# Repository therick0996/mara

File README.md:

# Patrick

**USE AT YOUR OWN RISK!!!** I am not responsible for any dumb things you do. Like fry your computer, break anything, etc.

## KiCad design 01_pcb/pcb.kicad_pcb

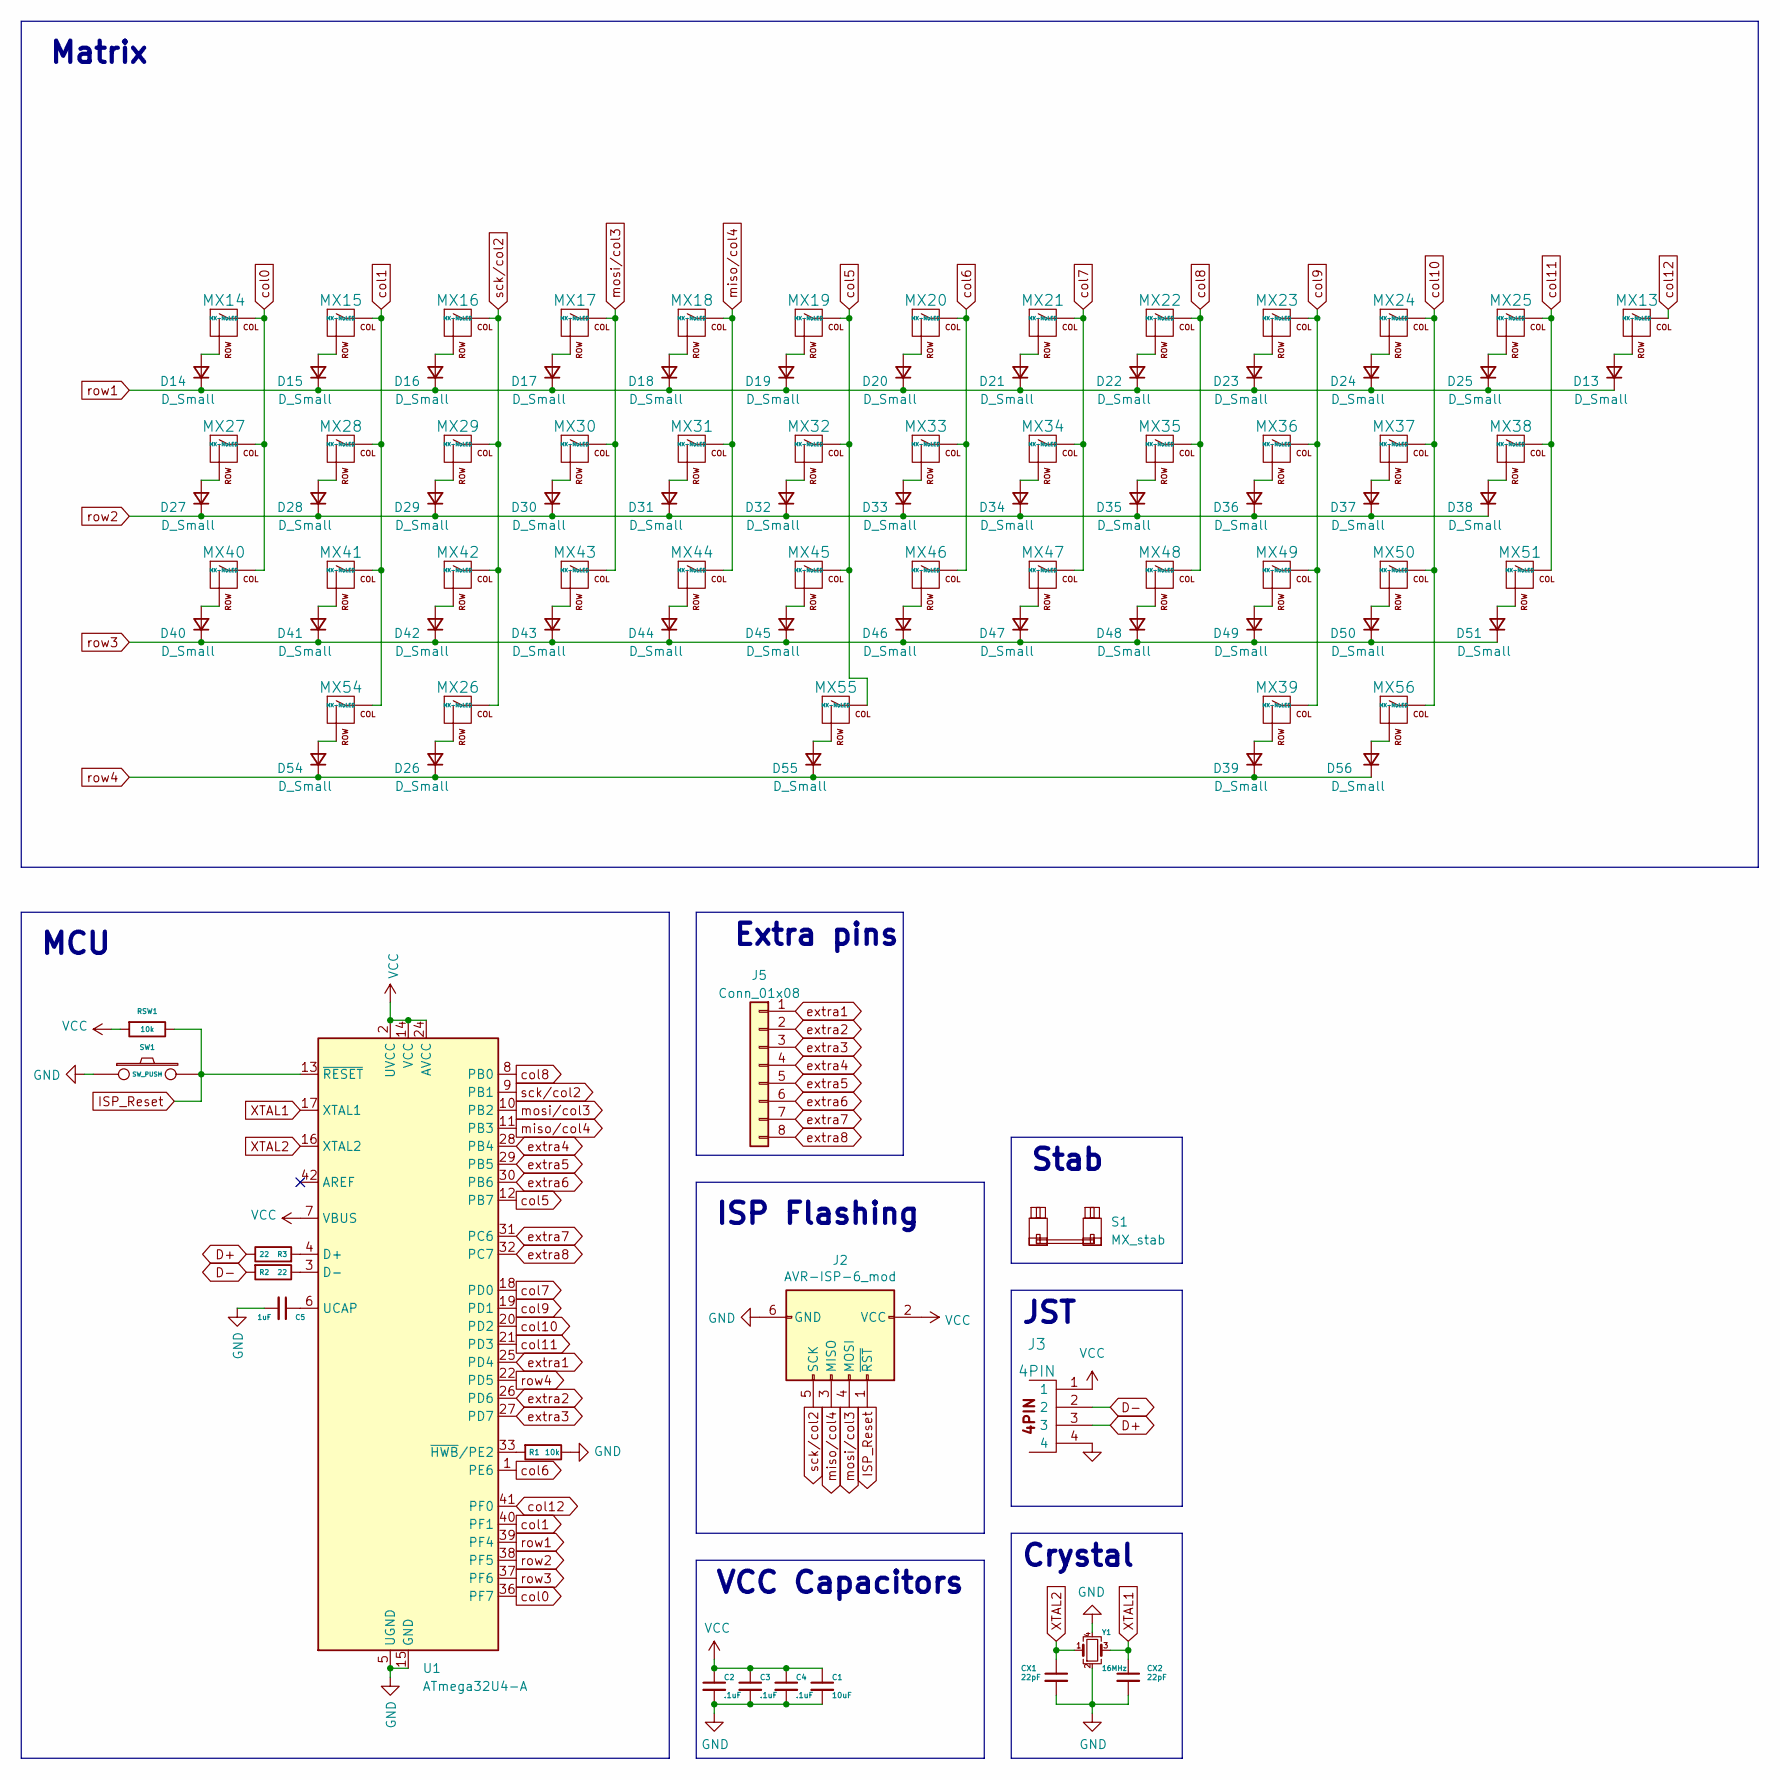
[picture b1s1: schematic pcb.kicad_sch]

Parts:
C1: 10uF; C_0805_2012Metric
C2, C3, C4: .1uF; C_0805_2012Metric
C5: 1uF; C_0805_2012Metric
CX1, CX2: 22pF; C_0805_2012Metric
D13, D14, D15, D16, D17, D18, D19, D20, D21, D22, D23, D24, D25, D26, D27, D28, D29, D30, D31, D32, D33, D34, D35, D36, D37, D38, D39, D40, D41, D42, D43, D44, D45, D46, D47, D48, D49, D50, D51, D54, D55, D56: D_Small; D_SOD-123
J2: AVR-ISP-6_mod; PinHeader_1x6_P2.54mm_Vertical
J3: 4PIN; JST_SH_SM04B-SRSS-TB_1x04-1MP_P1.00mm_Horizontal
J5: Conn_01x08; PinSocket_1x08_P2.54mm_Vertical
MX13, MX14, MX15, MX16, MX17, MX18, MX19, MX20, MX21, MX22, MX23, MX24, MX25, MX28, MX29, MX30, MX31, MX32, MX33, MX34, MX35, MX36, MX37, MX41, MX42, MX43, MX44, MX45, MX46, MX47, MX48, MX49, MX51, MX54, MX55, MX56: MX-NoLED; SW_MX_HS_1u
MX26, MX27, MX39, MX50: MX-NoLED; SW_MX_HS_1.25u
MX38, MX40: MX-NoLED; SW_MX_HS_1.75u
R1: 10k; R_0805_2012Metric
R2, R3: 22; R_0805_2012Metric
RSW1: 10k; R_0805_2012Metric
S1: MX_stab; STAB_MX_6.25u
SW1: SW_PUSH; SKQG-1155865
U1: ATmega32U4-A; TQFP-44_10x10mm_P0.8mm
Y1: 16MHz; Crystal_SMD_3225-4Pin_3.2x2.5mm

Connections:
D+: J3.3, R3.1
D-: J3.2, R2.2
GND: C1.2, C2.2, C3.2, C4.2, C5.2, CX1.2, CX2.2, J2.6 (GND), J3.4, R1.1, SW1.1, U1.5 (UGND), U1.15 (GND), U1.23 (GND), U1.35 (GND), U1.43 (GND), Y1.2, Y1.4
ISP_Reset: J2.1 (~RST), RSW1.1, SW1.2, U1.13 (~RESET)
unnamed: D13.2 (A), MX13.2 (ROW)
unnamed: D14.2 (A), MX14.2 (ROW)
unnamed: D15.2 (A), MX15.2 (ROW)
unnamed: D16.2 (A), MX16.2 (ROW)
unnamed: D17.2 (A), MX17.2 (ROW)
unnamed: D18.2 (A), MX18.2 (ROW)
unnamed: D19.2 (A), MX19.2 (ROW)
unnamed: D20.2 (A), MX20.2 (ROW)
unnamed: D21.2 (A), MX21.2 (ROW)
unnamed: D22.2 (A), MX22.2 (ROW)
unnamed: D23.2 (A), MX23.2 (ROW)
unnamed: D24.2 (A), MX24.2 (ROW)
unnamed: D25.2 (A), MX25.2 (ROW)
unnamed: D26.2 (A), MX26.2 (ROW)
unnamed: D27.2 (A), MX27.2 (ROW)
unnamed: D28.2 (A), MX28.2 (ROW)
unnamed: D29.2 (A), MX29.2 (ROW)
unnamed: D30.2 (A), MX30.2 (ROW)
unnamed: D31.2 (A), MX31.2 (ROW)
unnamed: D32.2 (A), MX32.2 (ROW)
unnamed: D33.2 (A), MX33.2 (ROW)
unnamed: D34.2 (A), MX34.2 (ROW)
unnamed: D35.2 (A), MX35.2 (ROW)
unnamed: D36.2 (A), MX36.2 (ROW)
unnamed: D37.2 (A), MX37.2 (ROW)
unnamed: D38.2 (A), MX38.2 (ROW)
unnamed: D39.2 (A), MX39.2 (ROW)
unnamed: D40.2 (A), MX40.2 (ROW)
unnamed: D41.2 (A), MX41.2 (ROW)
unnamed: D42.2 (A), MX42.2 (ROW)
unnamed: D43.2 (A), MX43.2 (ROW)
unnamed: D44.2 (A), MX44.2 (ROW)
unnamed: D45.2 (A), MX45.2 (ROW)
unnamed: D46.2 (A), MX46.2 (ROW)
unnamed: D47.2 (A), MX47.2 (ROW)
unnamed: D48.2 (A), MX48.2 (ROW)
unnamed: D49.2 (A), MX49.2 (ROW)
unnamed: D50.2 (A), MX50.2 (ROW)
unnamed: D51.2 (A), MX51.2 (ROW)
unnamed: D54.2 (A), MX54.2 (ROW)
unnamed: D55.2 (A), MX55.2 (ROW)
unnamed: D56.2 (A), MX56.2 (ROW)
unnamed: R3.2, U1.4 (D+)
unnamed: R2.1, U1.3 (D-)
unnamed: C5.1, U1.6 (UCAP)
unnamed: R1.2, U1.33 (~HWB/PE2)
VCC: C1.1, C2.1, C3.1, C4.1, J2.2 (VCC), J3.1, RSW1.2, U1.2 (UVCC), U1.7 (VBUS), U1.14 (VCC), U1.24 (AVCC), U1.34 (VCC), U1.44 (AVCC)
XTAL1: CX2.1, U1.17 (XTAL1), Y1.3
XTAL2: CX1.1, U1.16 (XTAL2), Y1.1
col0: MX14.1 (COL), MX27.1 (COL), MX40.1 (COL), U1.36 (PF7)
col1: MX15.1 (COL), MX28.1 (COL), MX41.1 (COL), MX54.1 (COL), U1.40 (PF1)
col5: MX19.1 (COL), MX32.1 (COL), MX45.1 (COL), MX55.1 (COL), U1.12 (PB7)
col6: MX20.1 (COL), MX33.1 (COL), MX46.1 (COL), U1.1 (PE6)
col7: MX21.1 (COL), MX34.1 (COL), MX47.1 (COL), U1.18 (PD0)
col8: MX22.1 (COL), MX35.1 (COL), MX48.1 (COL), U1.8 (PB0)
col9: MX23.1 (COL), MX36.1 (COL), MX39.1 (COL), MX49.1 (COL), U1.19 (PD1)
col10: MX24.1 (COL), MX37.1 (COL), MX50.1 (COL), MX56.1 (COL), U1.20 (PD2)
col11: MX25.1 (COL), MX38.1 (COL), MX51.1 (COL), U1.21 (PD3)
col12: MX13.1 (COL), U1.41 (PF0)
extra1: J5.1, U1.25 (PD4)
extra2: J5.2, U1.26 (PD6)
extra3: J5.3, U1.27 (PD7)
extra4: J5.4, U1.28 (PB4)
extra5: J5.5, U1.29 (PB5)
extra6: J5.6, U1.30 (PB6)
extra7: J5.7, U1.31 (PC6)
extra8: J5.8, U1.32 (PC7)
miso/col4: J2.3 (MISO), MX18.1 (COL), MX31.1 (COL), MX44.1 (COL), U1.11 (PB3)
mosi/col3: J2.4 (MOSI), MX17.1 (COL), MX30.1 (COL), MX43.1 (COL), U1.10 (PB2)
row1: D13.1 (K), D14.1 (K), D15.1 (K), D16.1 (K), D17.1 (K), D18.1 (K), D19.1 (K), D20.1 (K), D21.1 (K), D22.1 (K), D23.1 (K), D24.1 (K), D25.1 (K), U1.39 (PF4)
row2: D27.1 (K), D28.1 (K), D29.1 (K), D30.1 (K), D31.1 (K), D32.1 (K), D33.1 (K), D34.1 (K), D35.1 (K), D36.1 (K), D37.1 (K), D38.1 (K), U1.38 (PF5)
row3: D40.1 (K), D41.1 (K), D42.1 (K), D43.1 (K), D44.1 (K), D45.1 (K), D46.1 (K), D47.1 (K), D48.1 (K), D49.1 (K), D50.1 (K), D51.1 (K), U1.37 (PF6)
row4: D26.1 (K), D39.1 (K), D54.1 (K), D55.1 (K), D56.1 (K), U1.22 (PD5)
sck/col2: J2.5 (SCK), MX16.1 (COL), MX26.1 (COL), MX29.1 (COL), MX42.1 (COL), U1.9 (PB1)

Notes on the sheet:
ISP Flashing
Matrix
VCC Capacitors
Crystal
Extra pins
JST
Stab
MCU

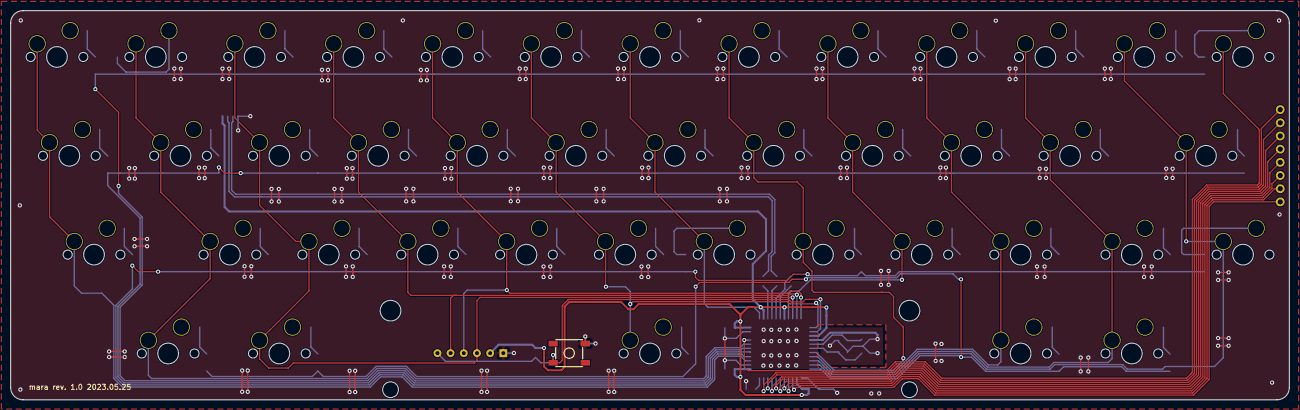
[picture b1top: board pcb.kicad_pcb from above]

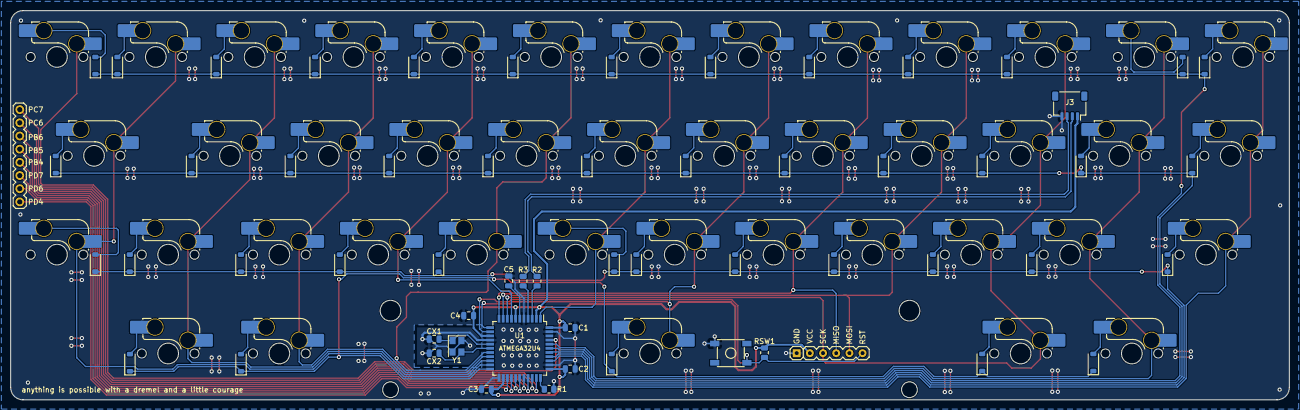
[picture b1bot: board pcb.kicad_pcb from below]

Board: 2 copper layers, 246.5 x 75.0 mm, 102 parts (102 on the bottom side), 78 nets.

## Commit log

2023-05-30 centered the bottom row
